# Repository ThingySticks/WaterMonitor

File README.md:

# WaterMonitor
Water usage monitor. Measure water usage and pipe temperature.

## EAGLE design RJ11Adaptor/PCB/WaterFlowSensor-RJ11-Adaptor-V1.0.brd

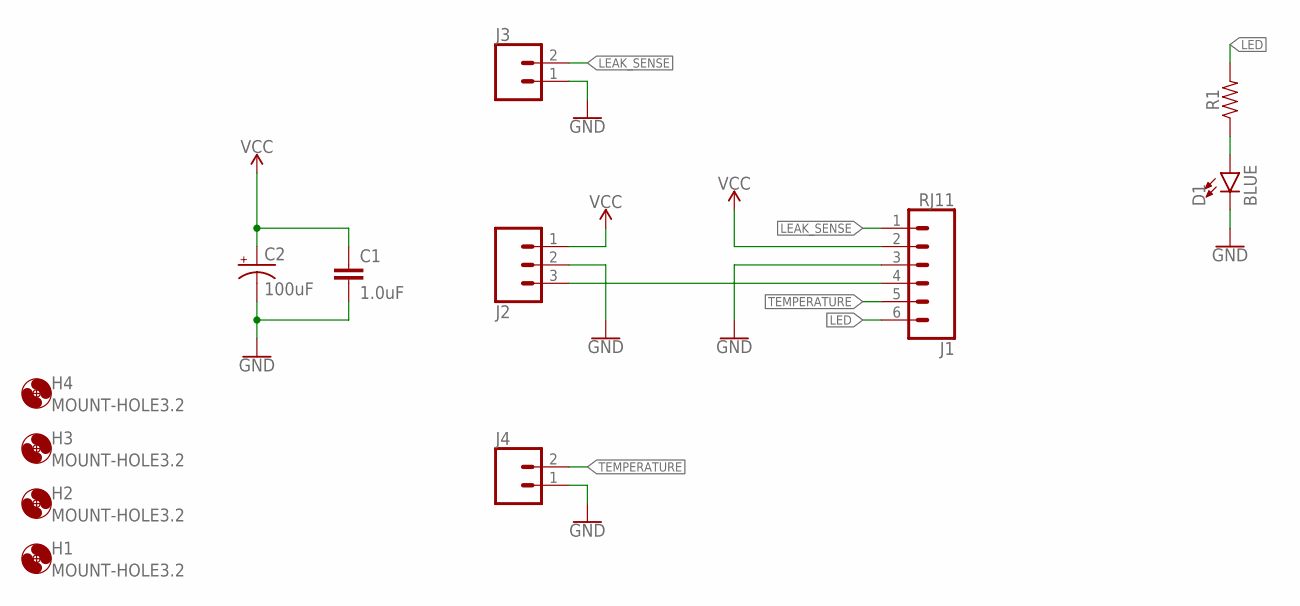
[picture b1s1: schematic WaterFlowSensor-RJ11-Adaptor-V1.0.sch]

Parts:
C1: 1.0uF; 0805
C2: 100uF; CPOL-RADIAL-2.5MM-6.5MM
D1: BLUE; LED-1206
H1, H2, H3, H4: MOUNT-HOLE3.2; 3,2
J1: RJ11; RJ11-6
J2: CONN_03JST-HX-PTH-VERT; JST-HX-3-PTH-VERT
J3: CONN_02; 1X02
J4: CONN_02POLAR; MOLEX-1X2
R1: 0805

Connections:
GND: C1.2, C2.2 (-), D1.C, J1.3, J2.2, J3.1, J4.1
LEAK_SENSE: J1.1, J3.2
LED: J1.6, R1.2
unnamed: D1.A, R1.1
unnamed: J1.4, J2.3
TEMPERATURE: J1.5, J4.2
VCC: C1.1, C2.1 (+), J1.2, J2.1

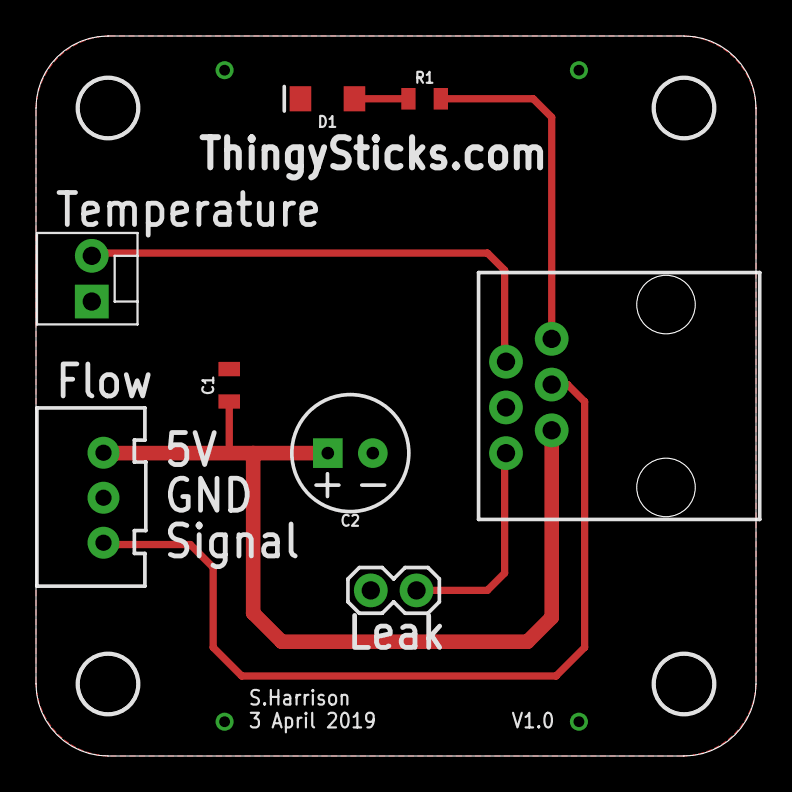
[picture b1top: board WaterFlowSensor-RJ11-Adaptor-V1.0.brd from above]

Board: 2 copper layers, 40.0 x 40.0 mm, 12 parts (0 on the bottom side), 7 nets.

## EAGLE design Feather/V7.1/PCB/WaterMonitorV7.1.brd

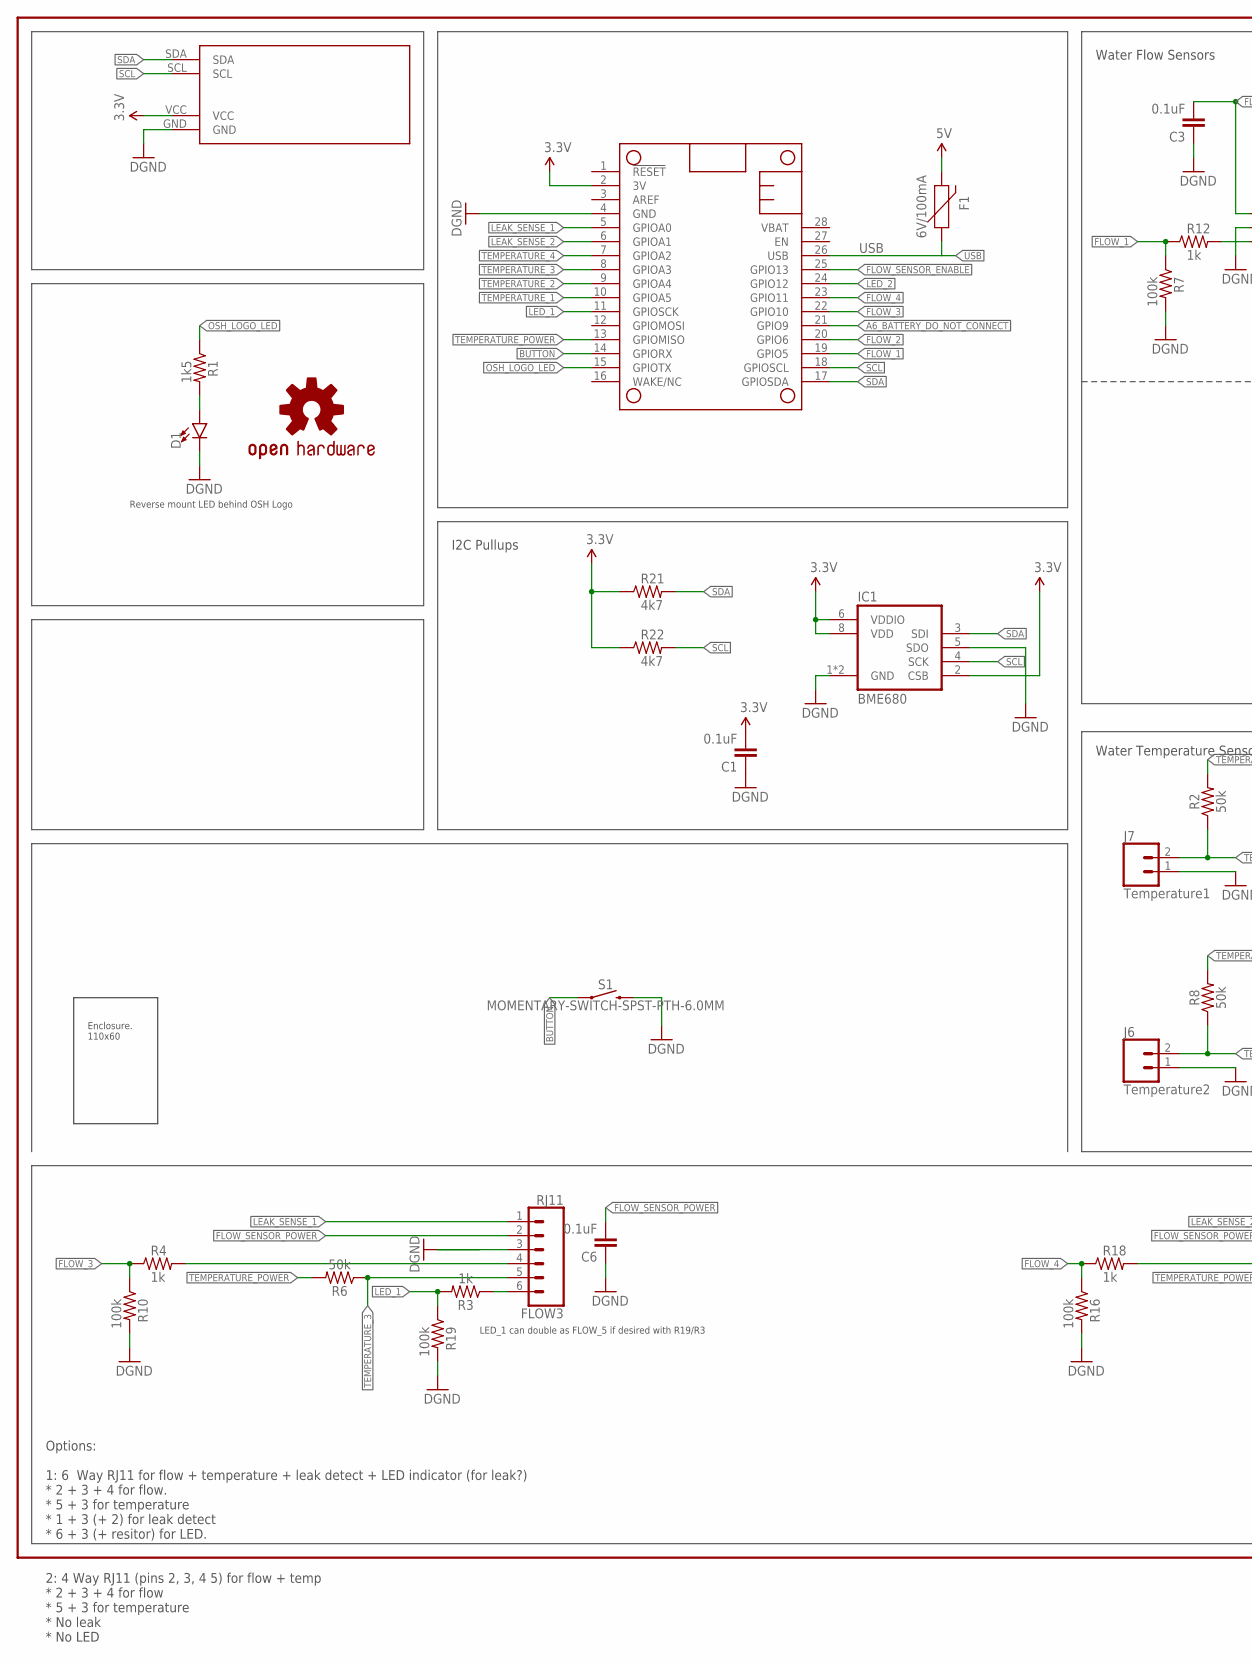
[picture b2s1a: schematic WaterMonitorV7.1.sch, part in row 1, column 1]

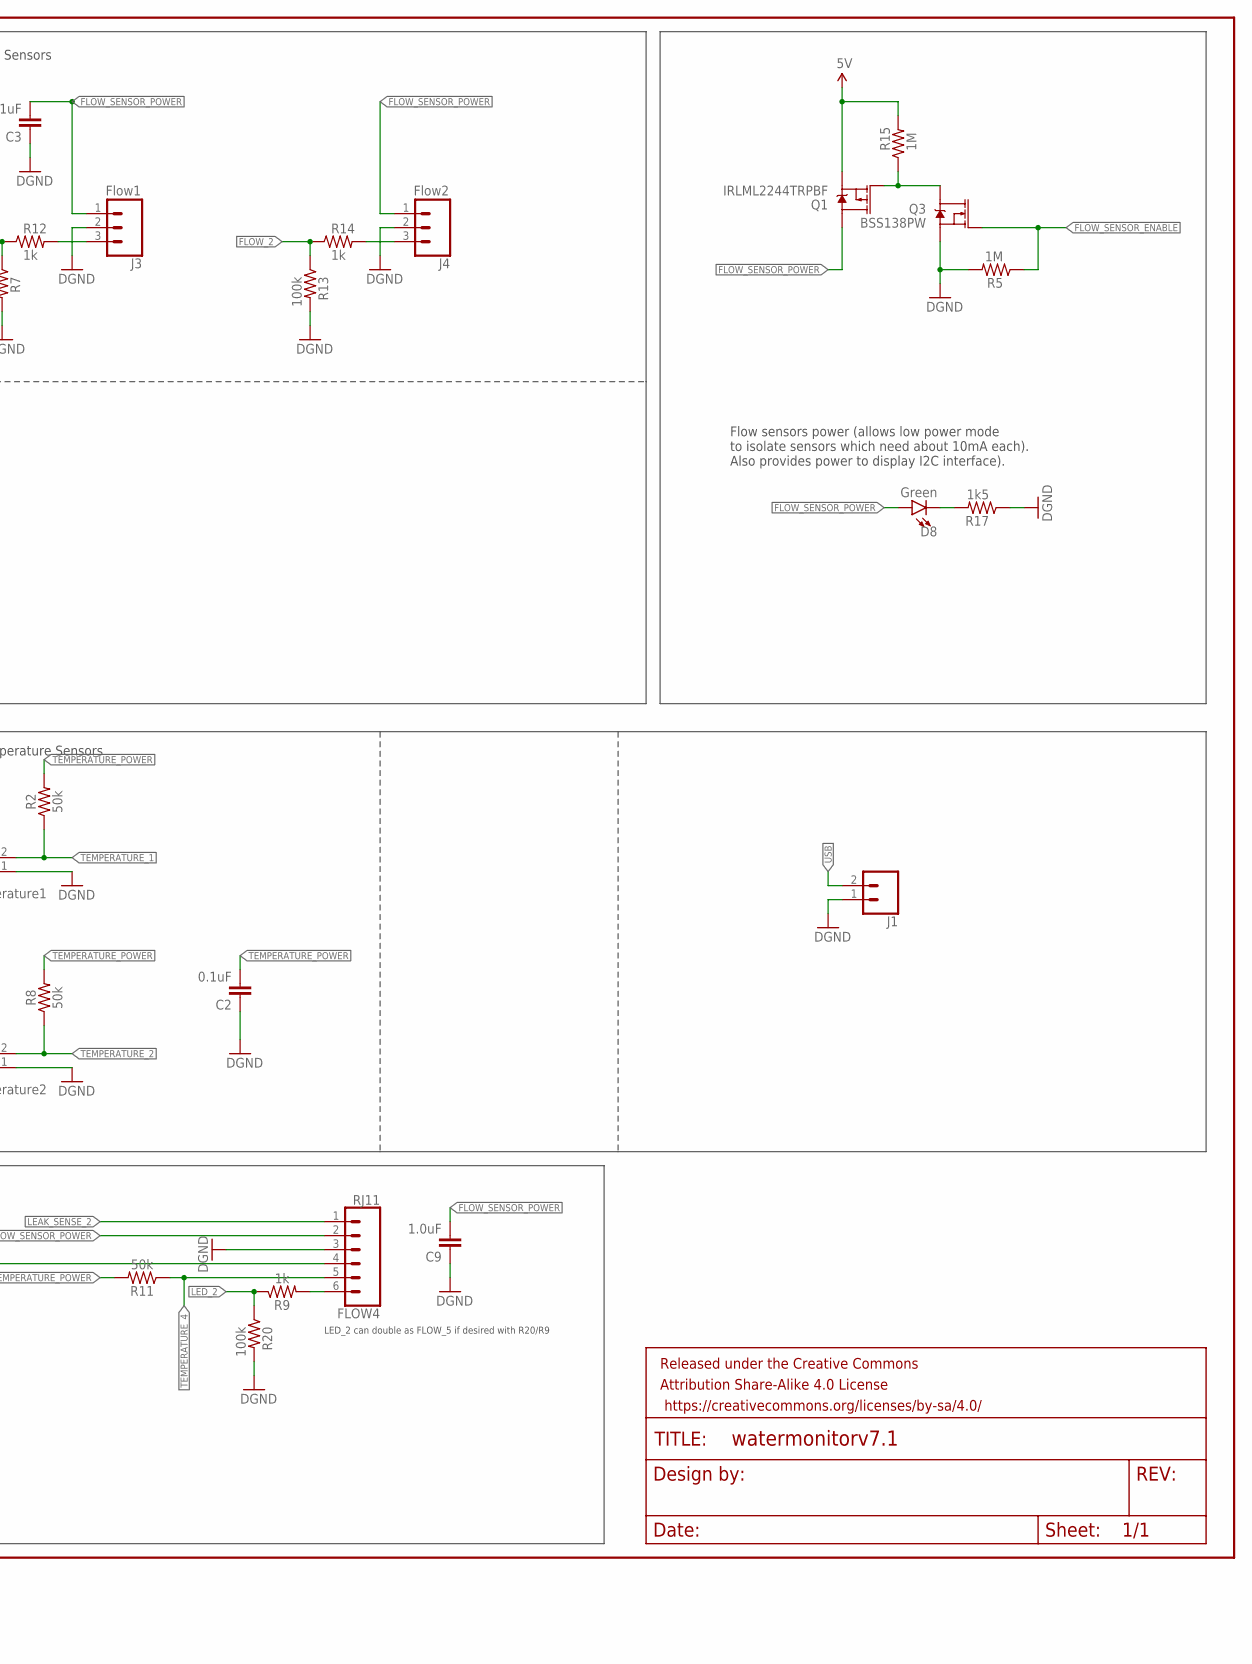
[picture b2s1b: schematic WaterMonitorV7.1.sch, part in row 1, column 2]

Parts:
C1, C2, C3, C6: 0.1uF; 0805
C9: 1.0uF; 0805
D1: LED1206-BOTTOM; LED-1206-BOTTOM
D8: Green; LED-1206
F1: 6V/100mA; 1206
FLOW3, FLOW4: RJ11; RJ11-6
FRAME2: FRAME-LEDGER; CREATIVE_COMMONS
IC1: BME680
J1: CONN_02-JST-2MM-SMT; JST-2-SMD
J3: Flow1; JST-HX-3-PTH-VERT; FARNELL 1516227
J4: Flow2; JST-HX-3-PTH-VERT; FARNELL 1516227
J6: Temperature2; MOLEX-1X2
J7: Temperature1; MOLEX-1X2
LOGO1: OSHW-LOGOM; OSHW-LOGO-M
MS1: FEATHERWINGSIMPLE; FEATHERWING_BREAKOUT_SIMPLE
Q1: IRLML2244TRPBF; SOT23-3; FARNELL 2468051
Q3: BSS138PW; SOT23-3; FARNELL 1907611
R1, R17: 1k5; 0805
R2, R6, R8, R11: 50k; 0805
R3, R4, R9, R12, R14, R18: 1k; 0805
R5, R15: 1M; 0805
R7, R10, R13, R16, R19, R20: 100k; 0805
R21, R22: 4k7; 0805
S1: MOMENTARY-SWITCH-SPST-PTH-6.0MM; TACTILE_SWITCH_PTH_6.0MM
U$1: CAMDENBOSS-ENCLOSURE-110X60BOTH-EXTENDED-WIDE; CAMDENBOSS_ENCLOSURE_110X60_WIDE_EXTENDED
U$2: DISPLAY0.96_INCH_DISPLAY; I2C_DISPLAY_0.96_INCH

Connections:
3.3V: C1.2, IC1.2 (CSB), IC1.6 (VDDIO), IC1.8 (VDD), MS1.2 (3V), R21.1, R22.1, U$2.VCC
5V: F1.2, Q1.2 (S), R15.2
A6_BATTERY_DO_NOT_CONNECT: MS1.21 (GPIO9)
BUTTON: MS1.14 (GPIORX), S1.1
FLOW_1: MS1.19 (GPIO5), R7.1, R12.1
FLOW_2: MS1.20 (GPIO6), R13.1, R14.1
FLOW_3: MS1.22 (GPIO10), R4.1, R10.1
FLOW_4: MS1.23 (GPIO11), R16.1, R18.1
FLOW_SENSOR_ENABLE: MS1.25 (GPIO13), Q3.1 (G), R5.1
FLOW_SENSOR_POWER: C3.2, C6.2, C9.2, D8.A, FLOW3.2, FLOW4.2, J3.1, J4.1, Q1.3 (D)
GND: C1.1, C2.1, C3.1, C6.1, C9.1, D1.C, FLOW3.3, FLOW4.3, IC1.1 (GND), IC1.5 (SDO), IC1.7 (GND), J1.1 (2), J3.2, J4.2, J6.1, J7.1, MS1.4 (GND), Q3.2 (S), R5.2, R7.2, R10.2, R13.2, R16.2, R17.1, R19.2, R20.2, S1.3 (2), U$2.GND
LEAK_SENSE_1: FLOW3.1, MS1.5 (GPIOA0)
LEAK_SENSE_2: FLOW4.1, MS1.6 (GPIOA1)
LED_1: MS1.11 (GPIOSCK), R3.2, R19.1
LED_2: MS1.24 (GPIO12), R9.1, R20.1
unnamed: J3.3, R12.2
unnamed: FLOW4.4, R18.2
unnamed: FLOW3.4, R4.2
unnamed: J4.3, R14.2
unnamed: D8.C, R17.2
unnamed: FLOW3.6, R3.1
unnamed: FLOW4.6, R9.2
unnamed: Q1.1 (G), Q3.3 (D), R15.1
unnamed: D1.A, R1.2
OSH_LOGO_LED: MS1.15 (GPIOTX), R1.1
SCL: IC1.4 (SCK), MS1.18 (GPIOSCL), R22.2, U$2.SCL
SDA: IC1.3 (SDI), MS1.17 (GPIOSDA), R21.2, U$2.SDA
TEMPERATURE_1: J7.2, MS1.10 (GPIOA5), R2.1
TEMPERATURE_2: J6.2, MS1.9 (GPIOA4), R8.1
TEMPERATURE_3: FLOW3.5, MS1.8 (GPIOA3), R6.1
TEMPERATURE_4: FLOW4.5, MS1.7 (GPIOA2), R11.1
TEMPERATURE_POWER: C2.2, MS1.13 (GPIOMISO), R2.2, R6.2, R8.2, R11.2
USB: F1.1, J1.2 (1), MS1.26 (USB)

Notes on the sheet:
Water Flow Sensors
Reverse mount LED behind OSH Logo
Water Temperature Sensors
Flow sensors power (allows low power mode to isolate sensors which need about 10mA each). Also provides power to display I2C interface).
Options: 1: 6 Way RJ11 for flow + temperature + leak detect + LED indicator (for leak?) * 2 + 3 + 4 for flow. * 5 + 3 for temperature * 1 + 3 (+ 2) for leak detect * 6 + 3 (+ resitor) for LED. 2: 4 Way RJ11 (pins 2, 3, 4 5) for flow + temp * 2 + 3 + 4 for flow * 5 + 3 for temperature * No leak * No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
LED_1 can double as FLOW_5 if desired with R19/R3
LED_2 can double as FLOW_5 if desired with R20/R9
I2C Pullups

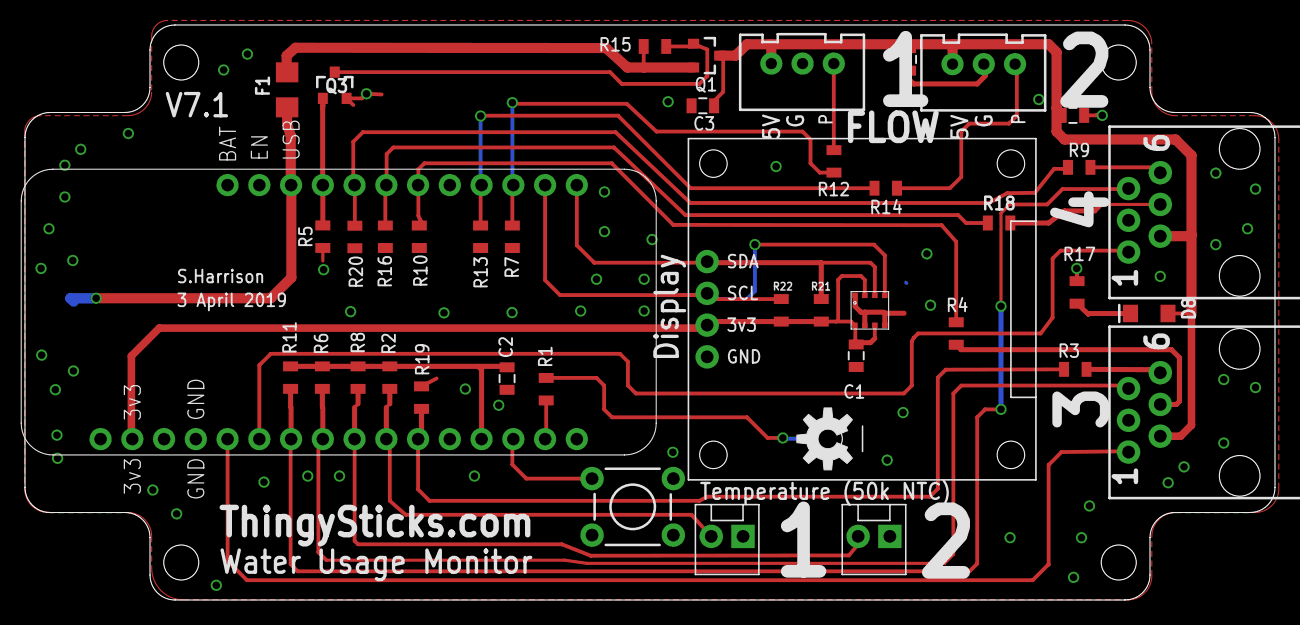
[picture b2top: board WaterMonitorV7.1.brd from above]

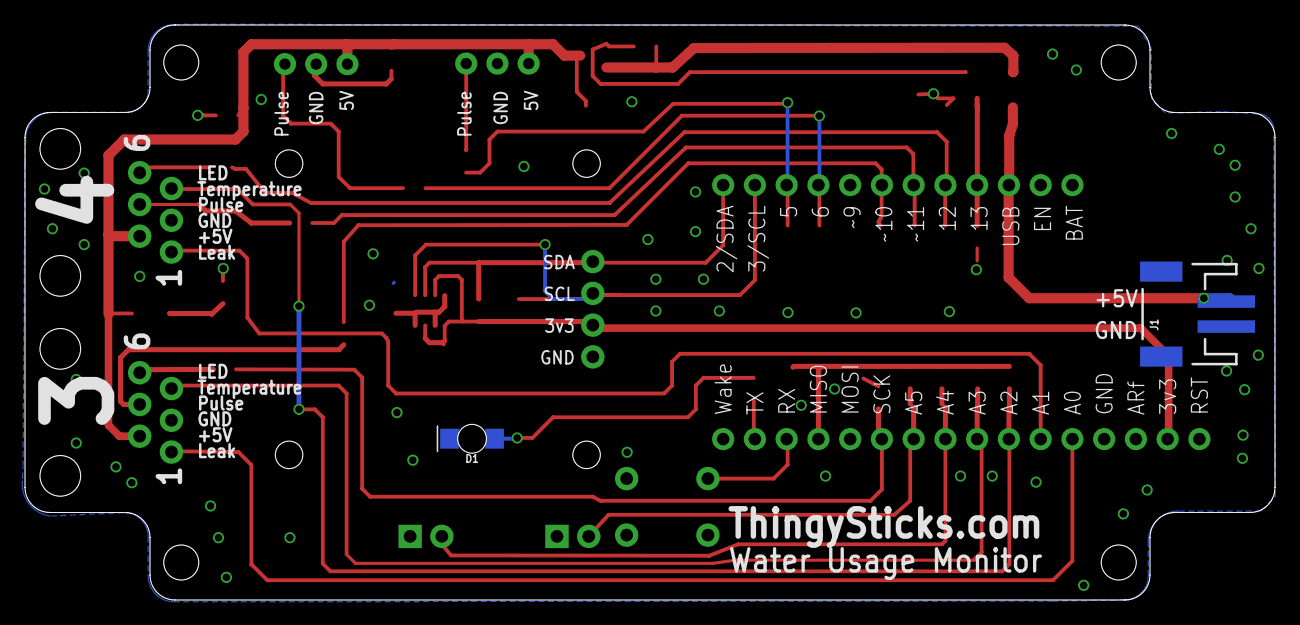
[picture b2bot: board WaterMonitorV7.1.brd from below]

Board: 2 copper layers, 100.0 x 46.0 mm, 46 parts (2 on the bottom side), 32 nets.

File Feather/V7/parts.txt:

Partlist

Exported from WaterMonitorV7.0.brd at 11/02/2019 21:43

EAGLE Version 7.4.0 Copyright (c) 1988-2015 CadSoft

Assembly variant: 

Part     Value                           Package                     Library               Position (inch)       Orientation

C1       0.1uF                           0805                        SparkFun-Passives     (2.781 0.856)         R270
C2       0.1uF                           0805                        SparkFun-Passives     (1.5109252 0.68533465) R180
C3       0.1uF                           0805                        SparkFun-Passives     (2.1359252 1.55610236) R0
C6       0.1uF                           0805                        SparkFun-Passives     (2.78395669 1.70226378) R90
C9       1.0uF                           0805                        SparkFun-Passives     (3.3015748 1.54389764) R180
D1                                       LED-1206-BOTTOM             SparkFun-LED          (3.17992126 0.13238189) MR180
D8       Green                           LED-1206                    SparkFun-LED          (3.54193307 0.90206299) R180
F1       6V/100mA                        1206                        SparkFun-Fuses        (0.8015748 1.60639764) R90
FLOW3    RJ11                            RJ11-6                      SparkFun-Connectors   (3.82677165 0.59055118) R90
FLOW4    RJ11                            RJ11-6                      SparkFun-Connectors   (3.82677165 1.22047244) R90
IC1      BME680                          BME680                      ThingySticks          (2.662 0.912)         R180
J3       Flow1                           JST-HX-3-PTH-VERT           Tinamous              (2.64685039 1.78169291) R180
J4       Flow2                           JST-HX-3-PTH-VERT           Tinamous              (3.21771654 1.77992126) R180
J6       Temperature2                    MOLEX-1X2                   SparkFun-Connectors   (2.725 0.175)         R180
J7       Temperature1                    MOLEX-1X2                   SparkFun-Connectors   (2.2625 0.175)        R180
MS1      FEATHERWINGSIMPLE               FEATHERWING_BREAKOUT_SIMPLE ThingySticks          (-0.0109252 0.45639764) R0
Q1       4.3A/20V/54m?                   SOT23-3                     SparkFun-DiscreteSemi (2.14606299 1.71417323) R270
Q3       220mA/50V/3.5?                  SOT23-3                     SparkFun-DiscreteSemi (0.9765748 1.61889764) R0
R1       1k5                             0805                        SparkFun-Resistors    (1.33839764 0.3964252) R270
R2       50k                             0805                        SparkFun-Resistors    (1.15 0.725)          R90
R3       1k                              0805                        SparkFun-Resistors    (3.309 0.726)         R180
R4       1k                              0805                        SparkFun-Resistors    (2.934 0.839)         R270
R5       1M                              0805                        SparkFun-Resistors    (0.9390748 1.16889764) R270
R6       50k                             0805                        SparkFun-Resistors    (0.9375 0.725)        R90
R7       100k                            0805                        SparkFun-Resistors    (1.4390748 1.55639764) R90
R8       50k                             0805                        SparkFun-Resistors    (1.05 0.725)          R90
R9       1k                              0805                        SparkFun-Resistors    (3.32135433 1.36230315) R0
R10      100k                            0805                        SparkFun-Resistors    (1.1390748 1.55639764) R90
R11      50k                             0805                        SparkFun-Resistors    (0.8375 0.725)        R90
R12      1k                              0805                        SparkFun-Resistors    (1.98110236 1.4760748) R0
R13      100k                            0805                        SparkFun-Resistors    (1.5390748 1.55639764) R90
R14      1k                              0805                        SparkFun-Resistors    (2.70610236 1.3765748) R0
R15      1M                              0805                        SparkFun-Resistors    (1.9851378 1.74311024) R180
R16      100k                            0805                        SparkFun-Resistors    (1.2390748 1.55639764) R90
R17      1k5                             0805                        SparkFun-Resistors    (3.31456693 0.96840551) R270
R18      1k                              0805                        SparkFun-Resistors    (3.069 1.187)         R0
R19      100k                            0805                        SparkFun-Resistors    (1.25 0.662)          R90
R20      100k                            0805                        SparkFun-Resistors    (1.035 1.457)         R90
R21      1k5                             0805                        SparkFun-Resistors    (2.509 0.912)         R90
R22      1k5                             0805                        SparkFun-Resistors    (2.383 0.912)         R90
S1       MOMENTARY-SWITCH-SPST-PTH-6.0MM TACTILE_SWITCH_PTH_6.0MM    SparkFun-Switches     (1.915 0.243)         R0
U$2      DISPLAY0.96_INCH_DISPLAY        I2C_DISPLAY_0.96_INCH       ThingySticks          (3.185 0.378)         R90

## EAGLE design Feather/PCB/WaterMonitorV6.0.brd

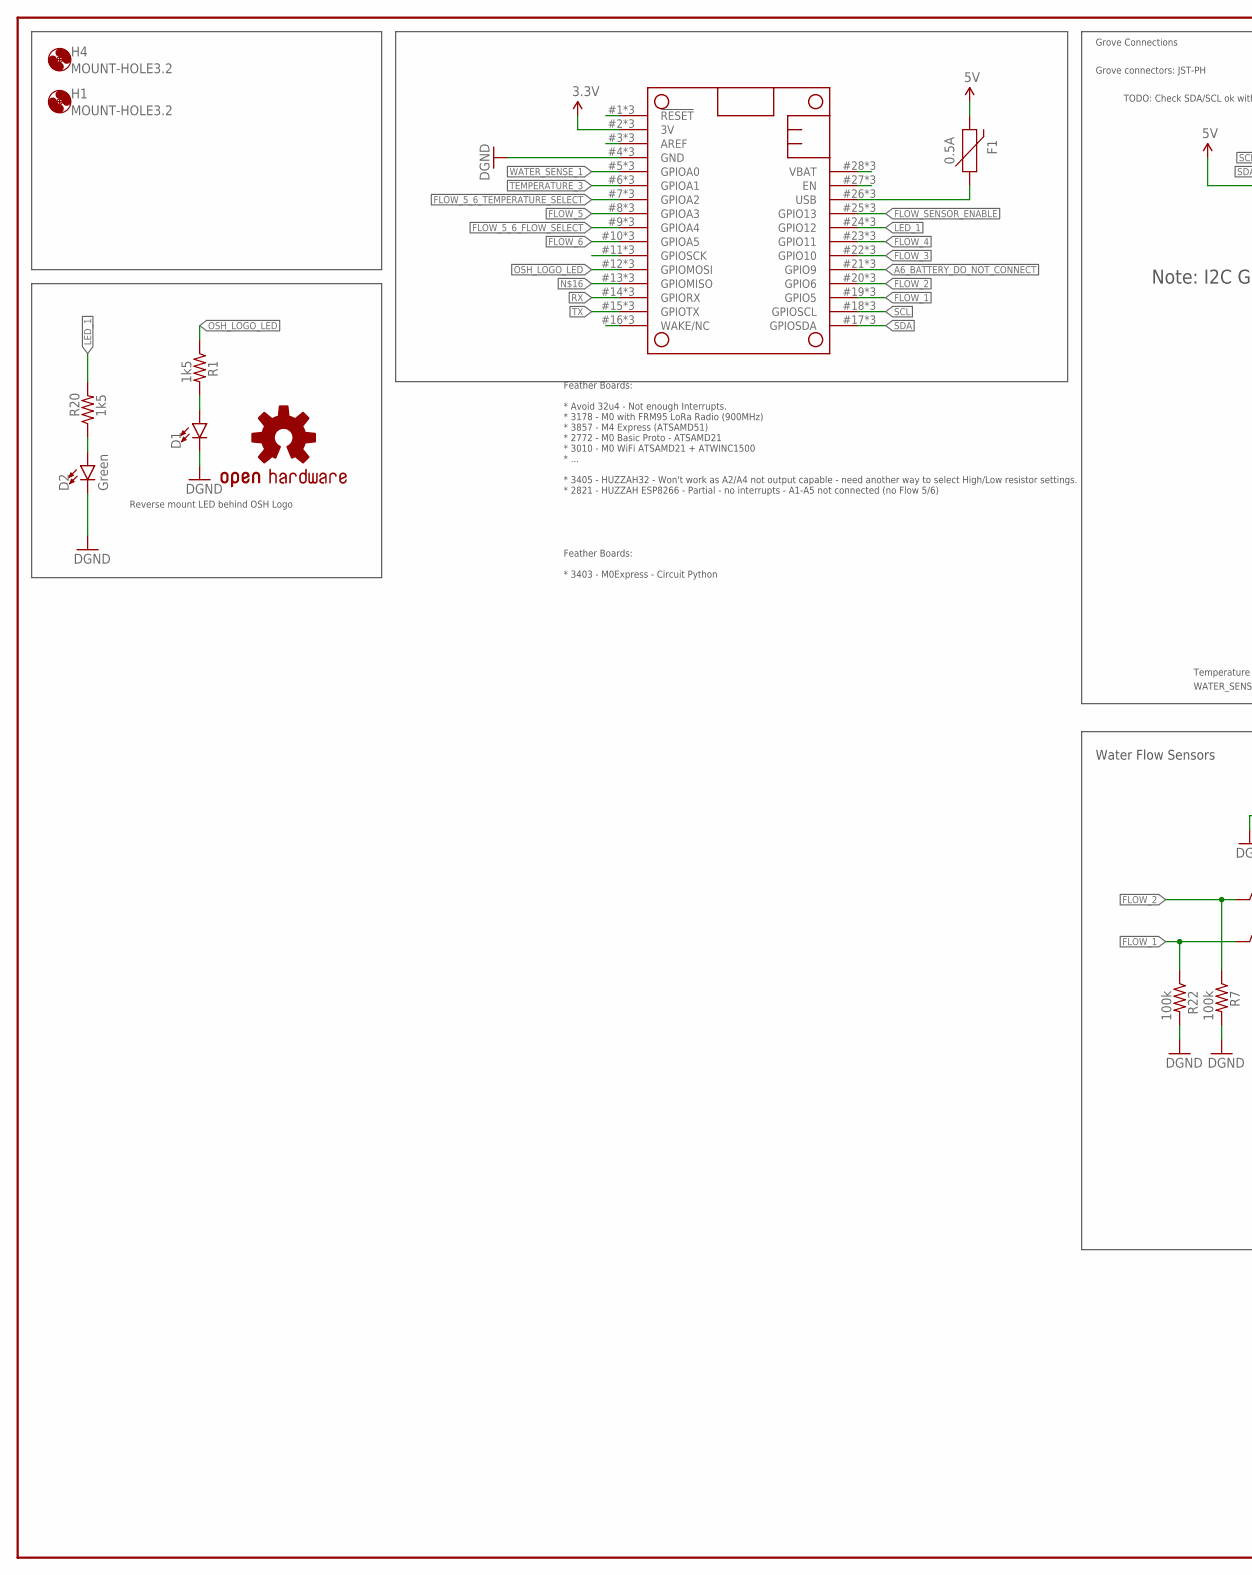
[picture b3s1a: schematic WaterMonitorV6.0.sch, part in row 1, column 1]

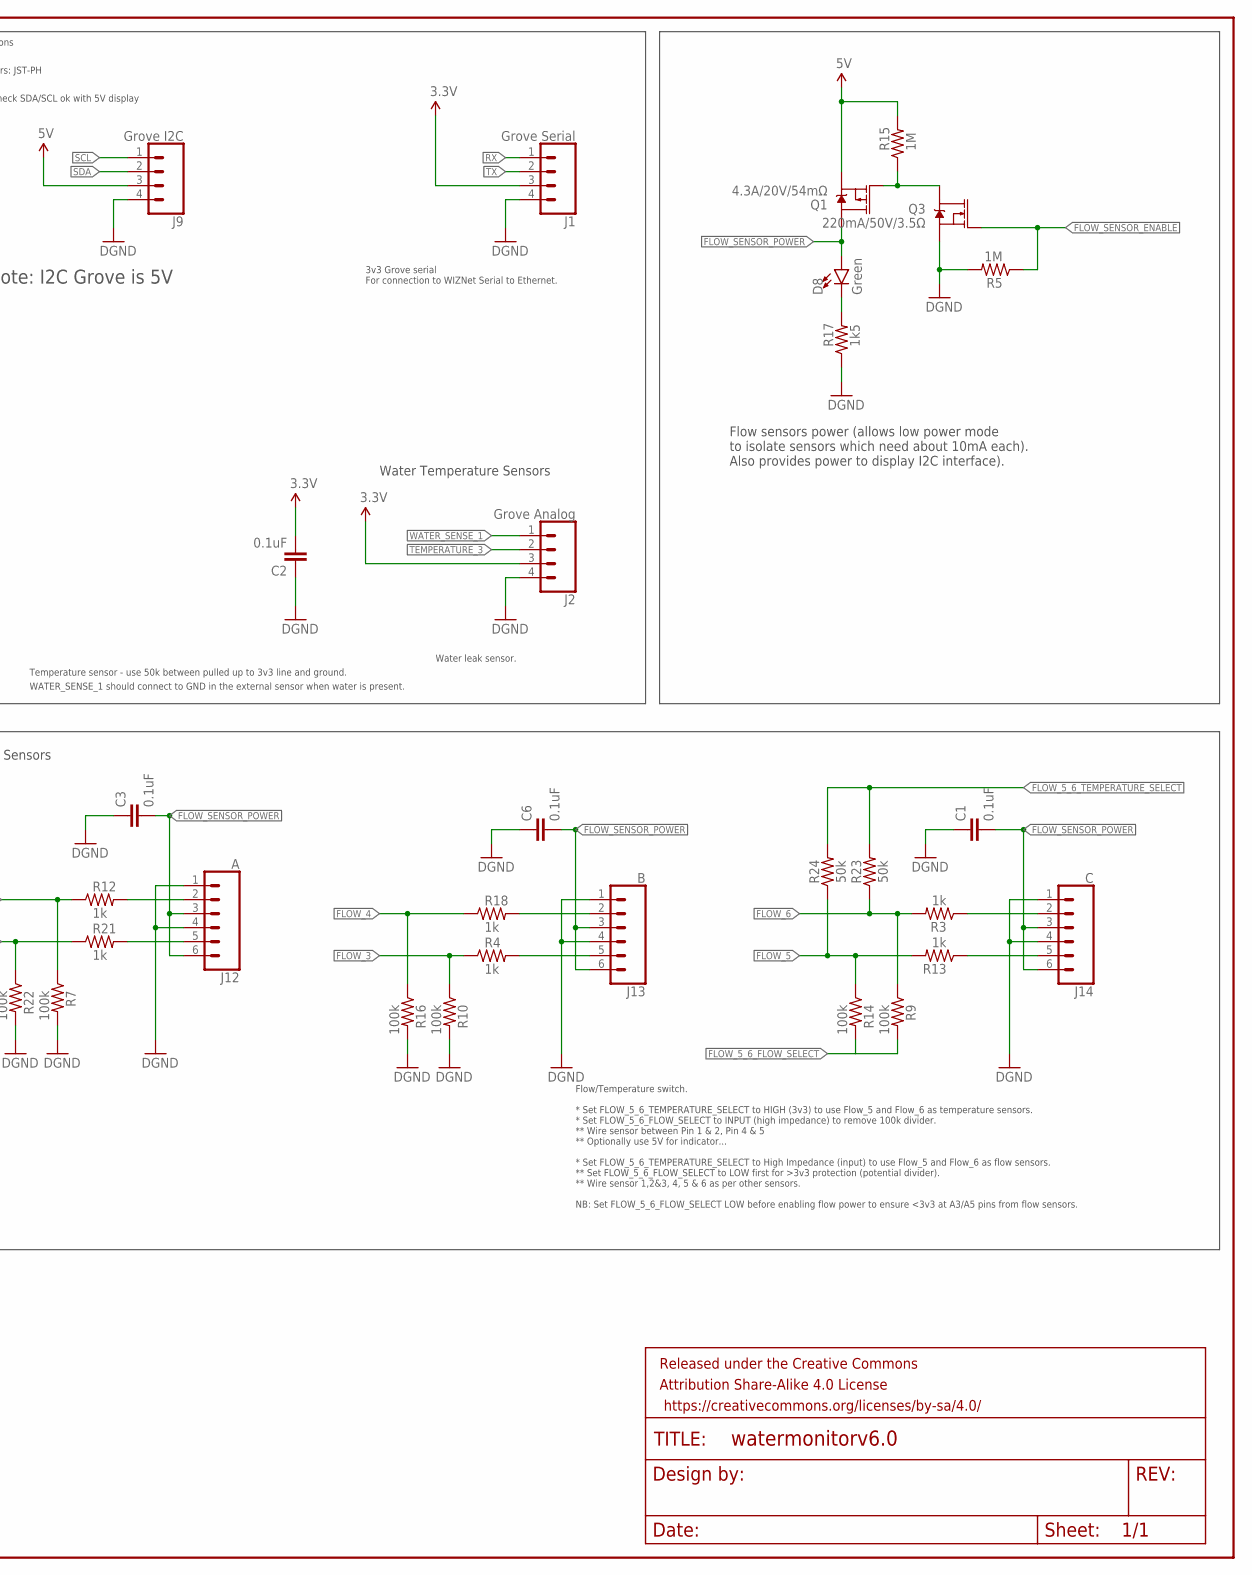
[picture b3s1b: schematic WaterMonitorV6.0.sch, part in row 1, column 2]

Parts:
C1, C2, C3, C6: 0.1uF; 0805
D1: LED1206-BOTTOM; LED-1206-BOTTOM
D2, D8: Green; LED-1206
F1: 0.5A; 1206
FRAME2: FRAME-LEDGER; CREATIVE_COMMONS
H1, H4: MOUNT-HOLE3.2; 3,2
J1: Grove Serial; JST-4-PTH-VERT
J2: Grove Analog; JST-4-PTH-VERT
J9: Grove I2C; JST-4-PTH-VERT
J12: A; RJ11-6
J13: B; RJ11-6
J14: C; RJ11-6
LOGO1: OSHW-LOGOM; OSHW-LOGO-M
MS1: FEATHERWINGFEATHEWING_BREAKOUT; FEATHERWING_BREAKOUT
Q1: 4.3A/20V/54mΩ; SOT23-3
Q3: 220mA/50V/3.5Ω; SOT23-3
R1, R17, R20: 1k5; 0805
R3, R4, R12, R13, R18, R21: 1k; 0805
R5, R15: 1M; 0805
R7, R9, R10, R14, R16, R22: 100k; 0805
R23, R24: 50k; 0805

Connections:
3.3V: C2.2, J1.3, J2.3, MS1.2 (3V), MS1.#2 (3V), MS1.@2 (3V)
5V: F1.2, J9.3, Q1.2 (S), R15.2
A6_BATTERY_DO_NOT_CONNECT: MS1.21 (GPIO9), MS1.#21 (GPIO9), MS1.@21 (GPIO9)
FLOW_1: MS1.19 (GPIO5), MS1.#19 (GPIO5), MS1.@19 (GPIO5), R21.1, R22.1
FLOW_2: MS1.20 (GPIO6), MS1.#20 (GPIO6), MS1.@20 (GPIO6), R7.1, R12.1
FLOW_3: MS1.22 (GPIO10), MS1.#22 (GPIO10), MS1.@22 (GPIO10), R4.1, R10.1
FLOW_4: MS1.23 (GPIO11), MS1.#23 (GPIO11), MS1.@23 (GPIO11), R16.1, R18.1
FLOW_5: MS1.8 (GPIOA3), MS1.#8 (GPIOA3), MS1.@8 (GPIOA3), R13.2, R14.1, R24.1
FLOW_5_6_FLOW_SELECT: MS1.9 (GPIOA4), MS1.#9 (GPIOA4), MS1.@9 (GPIOA4), R9.2, R14.2
FLOW_5_6_TEMPERATURE_SELECT: MS1.7 (GPIOA2), MS1.#7 (GPIOA2), MS1.@7 (GPIOA2), R23.2, R24.2
FLOW_6: MS1.10 (GPIOA5), MS1.#10 (GPIOA5), MS1.@10 (GPIOA5), R3.2, R9.1, R23.1
FLOW_SENSOR_ENABLE: MS1.25 (GPIO13), MS1.#25 (GPIO13), MS1.@25 (GPIO13), Q3.1 (G), R5.1
FLOW_SENSOR_POWER: C1.2, C3.2, C6.2, D8.A, J12.3, J12.6, J13.3, J13.6, J14.3, J14.6, Q1.3 (D)
GND: C1.1, C2.1, C3.1, C6.1, D1.C, D2.C, J1.4, J2.4, J9.4, J12.1, J12.4, J13.1, J13.4, J14.1, J14.4, MS1.4 (GND), MS1.#4 (GND), MS1.@4 (GND), Q3.2 (S), R5.2, R7.2, R10.2, R16.2, R17.1, R22.2
LED_1: MS1.24 (GPIO12), MS1.#24 (GPIO12), MS1.@24 (GPIO12), R20.2
unnamed: J12.5, R21.2
unnamed: J14.2, R3.1
unnamed: J13.5, R4.2
unnamed: J14.5, R13.1
unnamed: D8.C, R17.2
unnamed: D2.A, R20.1
unnamed: J12.2, R12.2
unnamed: MS1.1 (!RESET), MS1.#1 (!RESET), MS1.@1 (!RESET)
unnamed: MS1.27 (EN), MS1.#27 (EN), MS1.@27 (EN)
unnamed: MS1.13 (GPIOMISO), MS1.#13 (GPIOMISO), MS1.@13 (GPIOMISO)
unnamed: Q1.1 (G), Q3.3 (D), R15.1
unnamed: MS1.3 (AREF), MS1.#3 (AREF), MS1.@3 (AREF)
unnamed: D1.A, R1.2
unnamed: J13.2, R18.2
unnamed: MS1.11 (GPIOSCK), MS1.#11 (GPIOSCK), MS1.@11 (GPIOSCK)
unnamed: MS1.16 (WAKE/NC), MS1.#16 (WAKE/NC), MS1.@16 (WAKE/NC)
OSH_LOGO_LED: MS1.12 (GPIOMOSI), MS1.#12 (GPIOMOSI), MS1.@12 (GPIOMOSI), R1.1
RX: J1.1, MS1.14 (GPIORX), MS1.#14 (GPIORX), MS1.@14 (GPIORX)
SCL: J9.1, MS1.18 (GPIOSCL), MS1.#18 (GPIOSCL), MS1.@!8 (GPIOSCL)
SDA: J9.2, MS1.17 (GPIOSDA), MS1.#17 (GPIOSDA), MS1.@17 (GPIOSDA)
TEMPERATURE_3: J2.2, MS1.6 (GPIOA1), MS1.#6 (GPIOA1), MS1.@6 (GPIOA1)
TX: J1.2, MS1.15 (GPIOTX), MS1.#15 (GPIOTX), MS1.@15 (GPIOTX)
USB: F1.1, MS1.26 (USB), MS1.#26 (USB), MS1.@26 (USB)
VBAT: MS1.28 (VBAT), MS1.#28 (VBAT), MS1.@28 (VBAT)
WATER_SENSE_1: J2.1, MS1.5 (GPIOA0), MS1.#5 (GPIOA0), MS1.@5 (GPIOA0)

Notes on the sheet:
Water Flow Sensors
Reverse mount LED behind OSH Logo
Water leak sensor.
WATER_SENSE_1 should connect to GND in the external sensor when water is present.
TODO: Check SDA/SCL ok with 5V display
Water Temperature Sensors
Flow sensors power (allows low power mode to isolate sensors which need about 10mA each). Also provides power to display I2C interface).
Flow/Temperature switch. * Set FLOW_5_6_TEMPERATURE_SELECT to HIGH (3v3) to use Flow_5 and Flow_6 as temperature sensors. * Set FLOW_5_6_FLOW_SELECT to INPUT (high impedance) to remove 100k divider. ** Wire sensor between Pin 1 & 2, Pin 4 & 5 ** Optionally use 5V for indicator... * Set FLOW_5_6_TEM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
Temperature sensor - use 50k between pulled up to 3v3 line and ground.
3v3 Grove serial For connection to WIZNet Serial to Ethernet.
Grove connectors: JST-PH
Grove Connections
Note: I2C Grove is 5V
Feather Boards: * Avoid 32u4 - Not enough Interrupts. * 3178 - M0 with FRM95 LoRa Radio (900MHz) * 3857 - M4 Express (ATSAMD51) * 2772 - M0 Basic Proto - ATSAMD21 * 3010 - M0 WiFi ATSAMD21 + ATWINC1500 * ... * 3405 - HUZZAH32 - Won't work as A2/A4 not output capable - need another way to select Hig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
Feather Boards: * 3403 - M0Express - Circuit Python

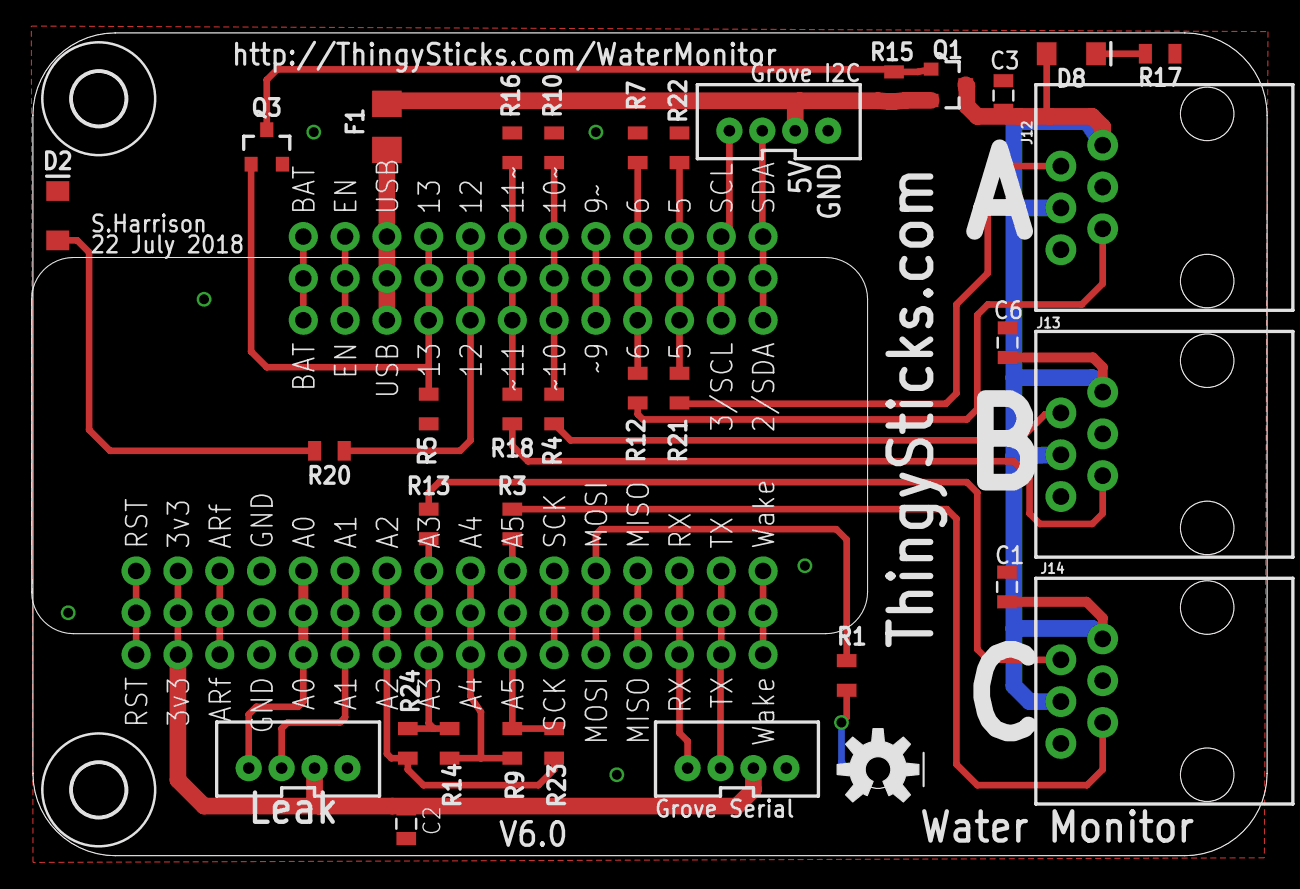
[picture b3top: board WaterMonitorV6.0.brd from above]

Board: 2 copper layers, 75.0 x 50.0 mm, 40 parts (1 on the bottom side), 40 nets.

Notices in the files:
parts and their libraries:
SparkFun-Connectors: Licensing: Creative Commons ShareAlike 4.0 International - https://creativecommons.org/licenses/by-sa/4.0
SparkFun-Aesthetics: Released under the Creative Commons Attribution Share-Alike 4.0 License
SparkFun-Aesthetics: https://creativecommons.org/licenses/by-sa/4.0
